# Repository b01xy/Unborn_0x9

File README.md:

# Unborn_0x9
Software for the projet Unborn 0x9 with Echopen device
* unb0rn12.pd  : audio patch sonification
* Unborn_0x9-Echopen_tcpclient-sonification-visualisation12.pd : video patch

More info : https://ressources.labomedia.org/unborn0x9_sonification_visualisation

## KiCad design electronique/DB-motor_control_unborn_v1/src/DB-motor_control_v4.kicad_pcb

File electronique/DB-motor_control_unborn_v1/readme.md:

# Daughter_board

## Name
[`DB-motor_control_unborn`]()

## Title
Daughter board motor control made for unborn0x9 project

## Author
* [`CTC-dubois_jerome`](), Future Baby Production

## Date
February 2020

## Interfaces
### Input
* [`ITF-A_gnd`]()
* [`ITF-B_5v`]()
* [`ITF-F_12v`]()
* [`ITF-S_3_3v`]()

### Output
* [`ITF-A_gnd`]()
* [`ITF-I_pulse_on`]()
* [`ITF-J_pulse_off`]()
* [`ITF-K_pulse_redpitaya`]()

##External connections
### Input
* GPIO DIO7_N of RedPitaya (connector E1) on P2
* GPIO DIO5_N of RedPitaya (connector E1) on P2
* GPIO DIO4_N of RedPitaya (connector E1) on P2
* GPIO DIO3_N of RedPitaya (connector E1) on P2
* GPIO DIO2_N of RedPitaya (connector E1) on P2
* GPIO DIO1_N of RedPitaya (connector E1) on P2
* GPIO DIO0_N of RedPitaya (connector E1) on P2

### Output
* stepper A1 on P5
* stepper A2 on P5
* stepper B1 on P5
* stepper B2 on P5

## Scheme

## Remarks
[BOM](./src/DB-motor_control_v3.csv)

This daughter board is for driving [28BYJ-48-12V] unipolar stepper motor(https://letmeknow.fr/shop/fr/moteurs-et-servo-moteurs/1520-petit-moteur-pas-a-pas-avec-reducteur-28byj-48-12v-700465391773.html) with an ULN2003 driver. We have change from bipolar to unipolar stepper motor, because old driver hash the 12V and produced a lot of noise. This motor has a 1/16 reductor so we have a angular precise enought and with the ULN2003 we can drive the motor without hash. So if we don't moove the motor during measuring acoustic line, it won't generate noise on signal. An arduino is pluged on socket P3 and P4 and the stepper motor is plugged on socket P5.

Socket P2 is used to connect the RedPitaya with this daughter_board such on following image. SN74 are used as level shifter for communication between RedPitaya (3.3 V) and arduino (5 V).

The piece on the left of the image can be cut from a matrix board like for the [mother board](../../../modules/hardware/MDL-mother_board/readme.md), the soldering track are on the top of this piece. There are two sockets 1*13 solder on it, don't forget to cut the tracks between these two socket (cut represent by the green line).

## Results

## Pros/Cons/Constraint:

**Pros:** NA

**Cons:** NA

**Constraint:** NA

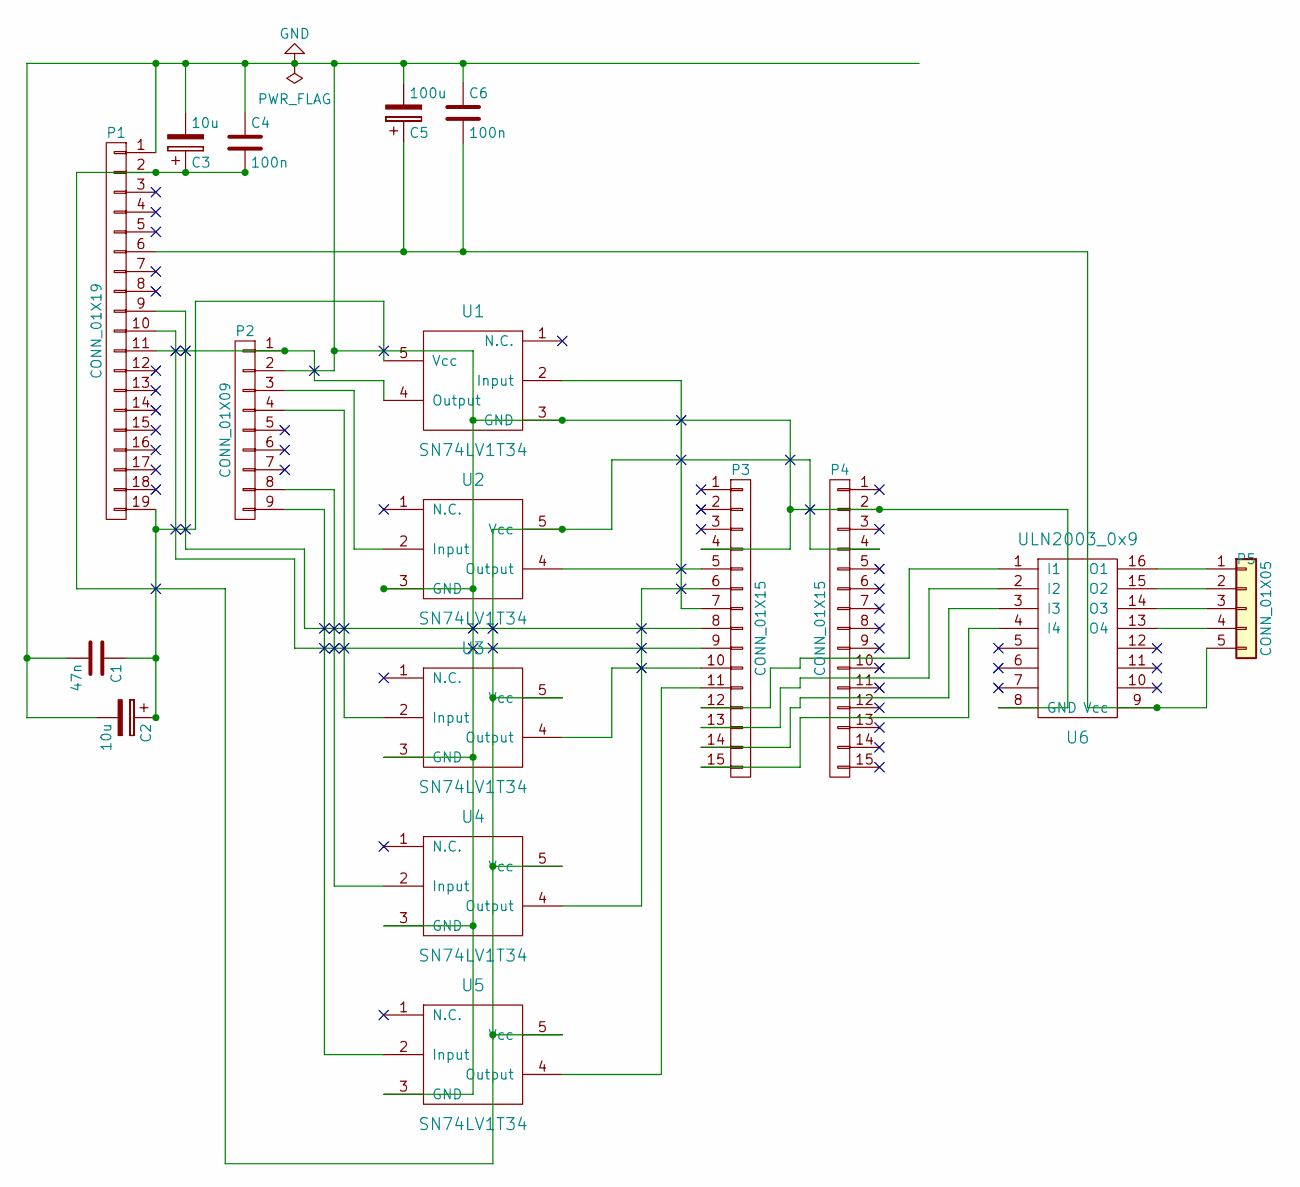
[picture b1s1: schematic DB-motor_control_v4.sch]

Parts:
C1: 47n; C_small_TH_echopen
C2, C3: 10u; CP_small_TH_echopen
C4, C6: 100n; C_small_TH_echopen
C5: 100u; CP_small_TH_echopen
P1: CONN_01X19; Header_pin_angled_1x19
P2: CONN_01X09; Socket_1x09
P3, P4: CONN_01X15; Pin_Header_Straight_1x15
P5: CONN_01X05; Socket_Strip_Straight_1x05_Pitch2.54mm
U1, U2, U3, U4, U5: SN74LV1T34; SOT-23-5_HandSoldering
U6: ULN2003_0x9; DIP-16_W7.62mm_LongPads

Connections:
GND: C1.2, C2.2, C3.2, C4.1, C5.2, C6.1, P1.1, P2.2, P3.4, P4.2, U1.3 (GND), U2.3 (GND), U3.3 (GND), U4.3 (GND), U5.3 (GND), U6.8 (GND)
unnamed: C1.1, C2.1, P1.19, U1.5 (Vcc)
unnamed: C3.1, C4.2, P1.2, P4.4, U2.5 (Vcc), U3.5 (Vcc), U4.5 (Vcc), U5.5 (Vcc)
unnamed: C5.1, C6.2, P1.6, P5.5, U6.9 (Vcc)
unnamed: P1.9, P3.8
unnamed: P1.10, P3.9
unnamed: P1.11, P2.1, U1.4 (Output)
unnamed: P2.3, U2.2 (Input)
unnamed: P2.4, U3.2 (Input)
unnamed: P2.8, U4.2 (Input)
unnamed: P2.9, U5.2 (Input)
unnamed: P3.5, U2.4 (Output)
unnamed: P3.6, U4.4 (Output)
unnamed: P3.7, U1.2 (Input)
unnamed: P3.10, U3.4 (Output)
unnamed: P3.11, U5.4 (Output)
unnamed: P3.12, U6.1 (I1)
unnamed: P3.13, U6.2 (I2)
unnamed: P3.14, U6.3 (I3)
unnamed: P3.15, U6.4 (I4)
unnamed: P5.1, U6.16 (O1)
unnamed: P5.2, U6.15 (O2)
unnamed: P5.3, U6.14 (O3)
unnamed: P5.4, U6.13 (O4)

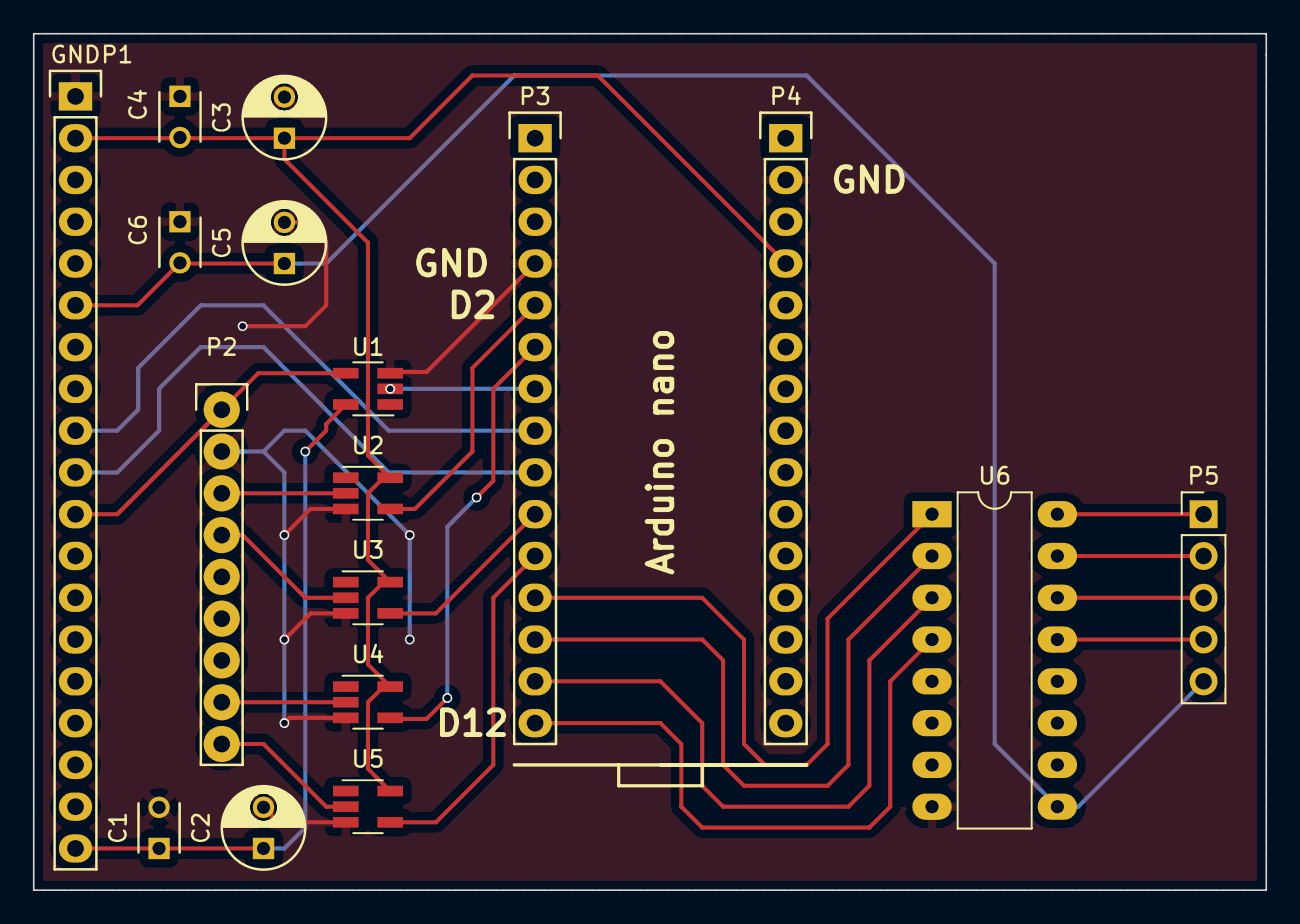
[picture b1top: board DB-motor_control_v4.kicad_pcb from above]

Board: 2 copper layers, 74.9 x 52.1 mm, 17 parts (0 on the bottom side), 24 nets.

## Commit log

2017-07-28 First Raw patch to get the datas from tcp redpitaya and produce sounds
2018-01-25 visualisation raw patch
2018-02-07 update audio and video patch after gaite lyrique performance
2018-02-08 add 4corners abstraction
2020-01-27 adding echopen code from 2017/2018
2020-01-28 petites améliorations et ajouts des tables enregistrées
2020-02-14 adding new daughter board for motor control
2020-02-18 first 3D model of the probe
2020-02-19 adding acoustic window in mechanism
2020-02-20 update 3D modeling
2020-02-23 update 3D
2020-02-23 update motor support to avoid transducer cable pinch
2020-03-18 correcting doc of motor control board
2020-03-19 adding arduino code of motor control board
2020-04-26 new redpitaya firmware
2020-04-26 creating GUI project with qtcreator
2020-09-25 Changement dans la réception des données, nouveaux générateurs de son
2020-10-04 Unborn0x9 patch sonification v12 - 10-2020
2020-10-04 Cleaning
2020-10-05 Modif connexion reseau
2020-10-05 Modif connexion reseau mrPeach
